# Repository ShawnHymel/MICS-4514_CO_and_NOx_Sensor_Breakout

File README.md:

MICS-4514_CO_and_NOx_Sensor_Breakout
==========================

Breakout board for the MiCS-4514 CO and NOx gas sensor.

Calculating CO and NOx Values
-----------------------------

I have not been able to work on this project in a few years, and at this point, I don't think I'll be able to continue the project in the foreseeable future (i.e. consider it a dead project). However, you are more than welcome to use the boards to make your own breakouts. If you are looking for example code on how to get CO and NOx readings, please [see this aricle](http://myscope.net/auswertung-der-airpi-gas-sensoren/) (in German, but the math should still work :).

Other example projects that calculate CO and NOx that might help you:

https://github.com/panStamp/swap/blob/master/examples/respira/sensor.h 
https://github.com/panStamp/swap/blob/master/examples/respira/sensor.ino
https://github.com/NationalAssociationOfRealtors/PiAQ/commit/cc4948cea3390a6df1ba7199cfc5aaa81f1222a6 
https://github.com/EmwareStd/Ventilation-system.-CO-and-NOx-control./blob/develop/Firmware/Sensor_module/Sensor_module.ino
https://github.com/Edvardoh/ArduinoAirQuality/blob/master/Arduino_NO2_CO_test/Arduino_NO2_CO_test.ino

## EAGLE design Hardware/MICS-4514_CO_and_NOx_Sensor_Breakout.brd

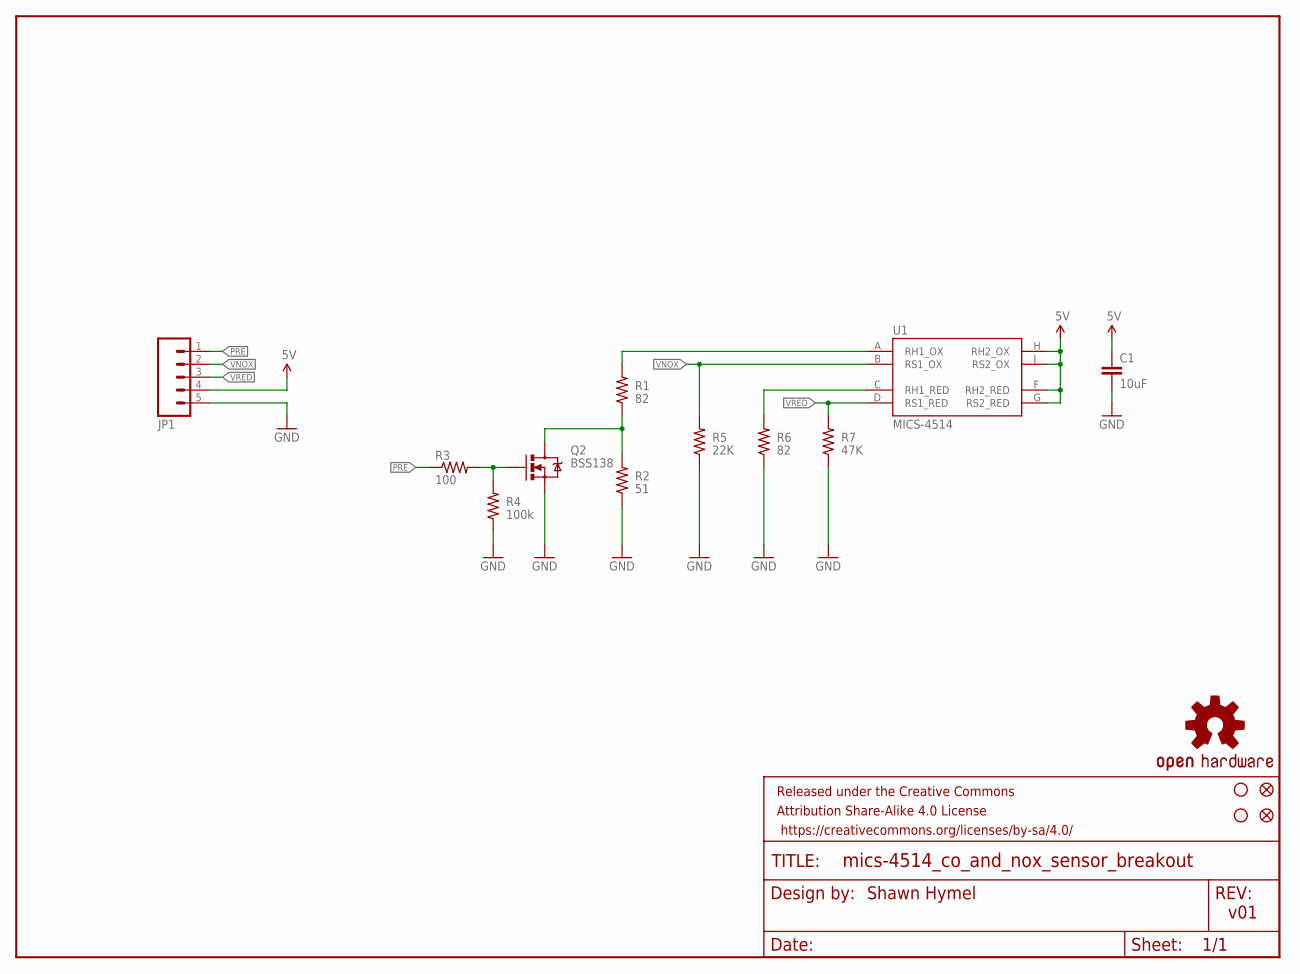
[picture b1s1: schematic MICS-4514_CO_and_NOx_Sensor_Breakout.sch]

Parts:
C1: 10uF; 0805
FID1, FID2: FIDUCIAL1X2; FIDUCIAL-1X2
FRAME1: FRAME-LETTER; CREATIVE_COMMONS
JP1: M05LOCK; 1X05_LOCK
LOGO1: OSHW-LOGOS; OSHW-LOGO-S
Q2: MOSFET-NCHANNELBSS138; SOT23-3
R1, R6: 82; 0805
R2: 51; 0603-RES
R3: 100; 0603-RES
R4: 100k; 0603-RES
R5: 22K; 0603-RES
R7: 47K; 0603-RES
STANDOFF3, STANDOFF5: STAND-OFF
U1: MICS-4514; MICS_10-SMD

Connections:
5V: C1.1, JP1.4, U1.F (RH2_RED), U1.G (RS2_RED), U1.H (RH2_OX), U1.J (RS2_OX)
GND: C1.2, JP1.5, Q2.2 (S), R2.1, R4.1, R5.1, R6.1, R7.1
unnamed: R1.2, U1.A (RH1_OX)
unnamed: R6.2, U1.C (RH1_RED)
unnamed: Q2.1 (G), R3.2, R4.2
unnamed: Q2.3 (D), R1.1, R2.2
PRE: JP1.1, R3.1
VNOX: JP1.2, R5.2, U1.B (RS1_OX)
VRED: JP1.3, R7.2, U1.D (RS1_RED)

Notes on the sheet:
v01
Shawn Hymel

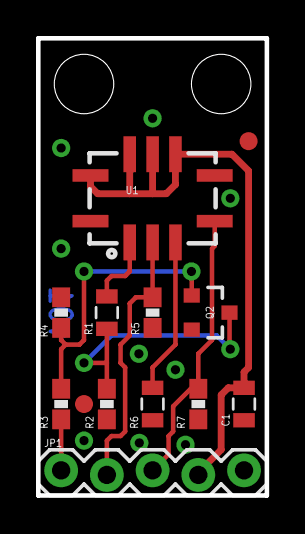
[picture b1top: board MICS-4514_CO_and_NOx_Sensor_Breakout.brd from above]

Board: 2 copper layers, 12.7 x 25.4 mm, 17 parts (1 on the bottom side), 9 nets.

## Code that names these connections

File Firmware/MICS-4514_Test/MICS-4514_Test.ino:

#define PRE_PIN          8
#define VNOX_PIN         A0
#define VRED_PIN         A1

#define PRE_HEAT_SECONDS 10

int vnox_value = 0;
int vred_value = 0;

void setup() {
  
  // Setup preheater pin
  pinMode(PRE_PIN, OUTPUT);
  
  // Initialize serial port
  Serial.begin(9600);
  Serial.println("MiCS-4514 Test Read");
  Serial.print("Preheating...");

  // Wait for preheating
  digitalWrite(PRE_PIN, 1);
  delay(PRE_HEAT_SECONDS * 1000);
  digitalWrite(PRE_PIN, 0);
  Serial.println("Done");
}

void loop() {
  
  // Read analog values, print them out, and wait
  vnox_value = analogRead(VNOX_PIN);
  vred_value = analogRead(VRED_PIN);
  Serial.print("Vnox: ");
  Serial.print(vnox_value, DEC);
  Serial.print(" Vred: ");
  Serial.println(vred_value, DEC);
  delay(1000);
}

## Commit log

2014-10-16 Copied in previous work.
2014-10-16 Deleted original files.
2014-10-16 Re-added files from previous work.
2014-10-16 Finished schematic. Added pre-heating FET.
2014-10-17 Created initial layout.
2014-10-21 Added BOM
2014-12-22 Added test Arduino code and photos.
2018-05-29 Update README.md
    Added note about where to find example code.
2018-06-20 Update README
    Added example code links

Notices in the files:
parts and their libraries:
SparkFun-Aesthetics: Licensing: Creative Commons ShareAlike 4.0 International - https://creativecommons.org/licenses/by-sa/4.0
SparkFun-Aesthetics: Released under the Creative Commons Attribution Share-Alike 4.0 License
SparkFun-Aesthetics: https://creativecommons.org/licenses/by-sa/4.0
